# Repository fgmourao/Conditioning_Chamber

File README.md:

# A Custom Microcontrolled and Wireless-Operated Chamber for Auditory Fear Conditioning

Front. Neurosci., 07 November 2019<br />
Sec. Neural Technology <br />
https://doi.org/10.3389/fnins.2019.01193<br />

Correspondence:<br />

Flávio Afonso Gonçalves Mourão, PhD<br />
Núcleo de Neurociências, Departamento de Fisiologia e Biofísica<br />
Instituto de Ciências Biológicas (ICB)<br /> 
Universidade Federal de Minas Gerais (UFMG)<br />
Av. Antônio Carlos, 6627 - CEP 31270-901- Campus Pampulha<br />
Belo Horizonte - MG - Brazil<br />
Fax: +55 31 3409-2924 Phone: +55 31 3409-2927<br />
Email:  mourao.fg@gmail.com / fagm@ufmg.br <br />

Márcio Flávio Dutra Moraes, PhD<br />
Núcleo de Neurociências, Departamento de Fisiologia e Biofísica<br />
Instituto de Ciências Biológicas (ICB)<br /> 
Universidade Federal de Minas Gerais (UFMG)<br />
Av. Antônio Carlos, 6627 - CEP 31270-901- Campus Pampulha<br />
Belo Horizonte - MG - Brazil<br />
Fax: +55 31 3409-2924 Phone: +55 31 3409-2930<br />
Email: mfdm@icb.ufmg.br <br />
<br />

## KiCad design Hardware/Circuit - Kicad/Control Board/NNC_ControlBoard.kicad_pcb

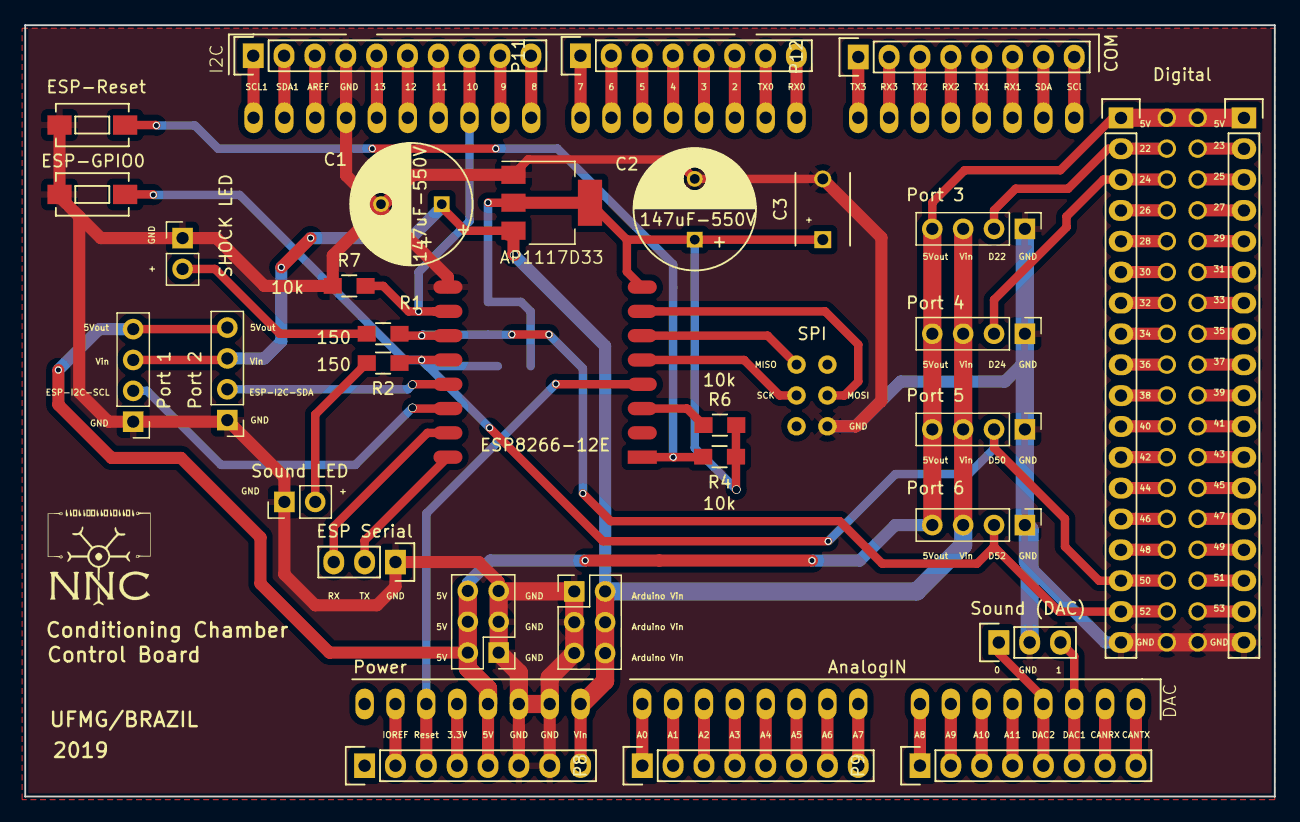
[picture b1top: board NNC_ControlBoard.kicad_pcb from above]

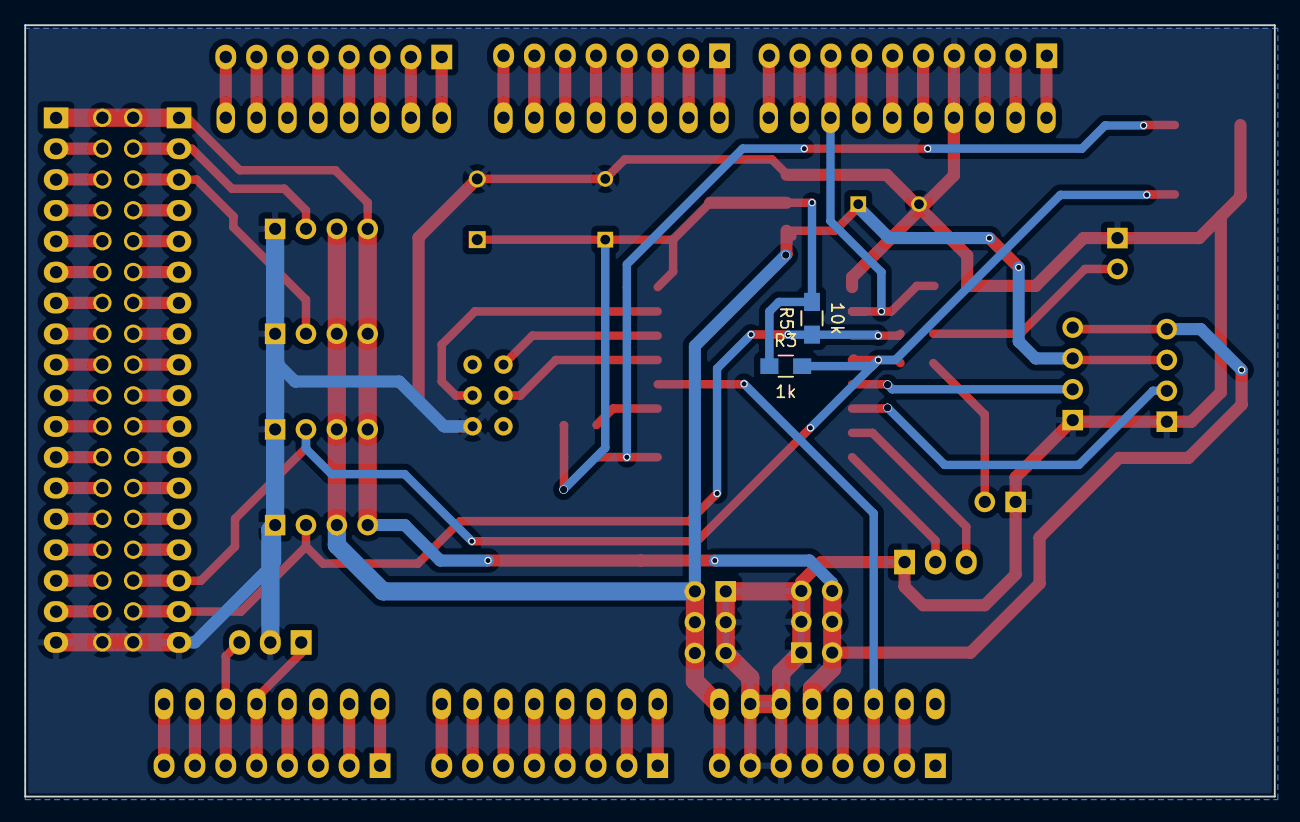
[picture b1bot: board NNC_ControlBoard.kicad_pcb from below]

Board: 2 copper layers, 102.9 x 63.5 mm, 35 parts (2 on the bottom side), 91 nets.

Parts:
C1, C2: 147uF-550V; C_Radial_D10_L13_P5
C3: C; C_Disc_D6_P5
Control Board: Conditioning Chamber; ARDUINO_DUE_SHIELD
D1: SHOCK LED; Pin_Header_Straight_1x02_Pitch2.54mm
D2: Sound LED; Pin_Header_Straight_1x02_Pitch2.54mm
ESP1: ESP8266-12E; ESP-12E_noBottomPads
ESP-GPIO0: 2; SW_SPST_EVQPE1
ESP-Reset: 1; SW_SPST_EVQPE1
I2C: PWM2; Pin_Header_Straight_1x10
J1: Port 6; Pin_Header_Straight_1x04_Pitch2.54mm
J2: Port 2; Pin_Header_Straight_1x04_Pitch2.54mm
J3: Port 3; Pin_Header_Straight_1x04_Pitch2.54mm
J4: Port 4; Pin_Header_Straight_1x04_Pitch2.54mm
J5: Port 5; Pin_Header_Straight_1x04_Pitch2.54mm
J6: Port 1; Pin_Header_Straight_1x04_Pitch2.54mm
J7: Arduino Vin; Pin_Header_Straight_2x03_Pitch2.54mm
J8: 5V; Pin_Header_Straight_2x03_Pitch2.54mm
P3: Sound (DAC); Pin_Header_Straight_1x03
P4: ESP Serial; Pin_Header_Straight_1x03
P5: DIG1; Pin_Header_Straight_1x18
P6: DIG2; Pin_Header_Straight_1x18
P7: Power; Pin_Header_Straight_1x08
P8: AnalogIN; Pin_Header_Straight_1x08
P9: DAC; Pin_Header_Straight_1x08
P11: PWM1; Pin_Header_Straight_1x08
P12: COM; Pin_Header_Straight_1x08
R1, R2: 150; R_0805_HandSoldering
R3: 1k; R_0805_HandSoldering
R4, R5, R6, R7: 10k; R_0805_HandSoldering
U1: AP1117D33; SOT-223-3_TabPin2

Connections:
/5Voutput: Control Board.5V, Control Board.5V_4, Control Board.5V_5, J1.4, J2.4, J3.4, J4.4, J5.4, J6.4, J8.2, J8.4, J8.6, P5.1, P6.1, P7.5
/Arduino_Vin: C1.1, Control Board.V_IN, J1.3, J2.3, J3.3, J4.3, J5.3, J6.3, J7.2, J7.4, J7.6, P7.8, U1.3
/D22: Control Board.22, J3.2, P5.2
/D23: Control Board.23, P6.2
/D24: Control Board.24, J4.2, P5.3
/D25: Control Board.25, P6.3
/D26: Control Board.26, P5.4
/D27: Control Board.27, P6.4
/D28: Control Board.28, P5.5
/D29: Control Board.29, P6.5
/D30: Control Board.30, P5.6
/D31: Control Board.31, P6.6
/D32: Control Board.32, P5.7
/D33: Control Board.33, P6.7
/D34: Control Board.34, P5.8
/D35: Control Board.35, P6.8
/D36: Control Board.36, P5.9
/D37: Control Board.37, P6.9
/D38: Control Board.38, P5.10
/D39: Control Board.39, P6.10
/D40: Control Board.40, P5.11
/D41: Control Board.41, P6.11
/D42: Control Board.42, P5.12
/D43: Control Board.43, P6.12
/D44: Control Board.44, P5.13
/D45: Control Board.45, P6.13
/D46: Control Board.46, P5.14
/D47: Control Board.47, P6.14
/D48: Control Board.48, P5.15
/D49: Control Board.49, P6.15
/D50: Control Board.50, ESP1.18, ESP-GPIO0.1, J5.2, P5.16, R2.1, R3.2
/D51: Control Board.51, P6.16
/D52: Control Board.52, ESP1.17, J1.2, P5.17, R1.1, R5.1
/D53: Control Board.53, P6.17
/DAC0: Control Board.DAC0, P3.1, P9.5
/DAC1: Control Board.DAC1, P3.3, P9.6
/ESP12Econfig/ESPchpd: ESP1.3, R6.1
/ESP12Econfig/ESPrst: ESP1.1, ESP-Reset.1, R4.2
/ESP12Econfig/VDD3V: C2.1, C3.1, ESP1.8, R3.1, R4.1, R5.2, R6.2, U1.2
/ESP_CS: Control Board.10, ESP1.16, I2C.8, R7.2
/ESP_GPIO16: Control Board.RST, ESP1.4, P7.3
/ESP_I2C_SCL: ESP1.20, J6.2
/ESP_I2C_SDA: ESP1.19, J2.2
/ESP_MISO: Control Board.SP1, ESP1.6
/ESP_MOSI: Control Board.SP4, ESP1.7
/ESP_RX: ESP1.21, P4.3
/ESP_SCK: Control Board.SP3, ESP1.5
/ESP_TX: ESP1.22, P4.2
/GND: C1.2, C2.2, C3.2, Control Board.GND1, Control Board.GND2, Control Board.GND3, Control Board.GND4, Control Board.GND5, Control Board.SP6, D1.1, D2.1, ESP1.15, ESP-GPIO0.2, ESP-Reset.2, I2C.4, J1.1, J2.1, J3.1, J4.1, J5.1, J6.1, J7.1, J7.3, J7.5, J8.1, J8.3, J8.5, P3.2, P4.1, P5.18, P6.18, P7.6, P7.7, R7.1, U1.1
unnamed: D1.2, R1.2
unnamed: D2.2, R2.2
unnamed: Control Board.IO_R, P7.2
unnamed: Control Board.3V3, P7.4
unnamed: Control Board.AD0, P8.1
unnamed: Control Board.AD1, P8.2
unnamed: Control Board.AD2, P8.3
unnamed: Control Board.AD3, P8.4
unnamed: Control Board.AD4, P8.5
unnamed: Control Board.AD5, P8.6
unnamed: Control Board.AD6, P8.7
unnamed: Control Board.AD7, P8.8
unnamed: Control Board.AD8, P9.1
unnamed: Control Board.AD9, P9.2
unnamed: Control Board.AD10, P9.3
unnamed: Control Board.AD11, P9.4
unnamed: Control Board.C_RX, P9.7
unnamed: Control Board.C_TX, P9.8
unnamed: Control Board.SCL1, I2C.1
unnamed: Control Board.SDA1, I2C.2
unnamed: Control Board.AREF, I2C.3
unnamed: Control Board.13, I2C.5
unnamed: Control Board.12, I2C.6
unnamed: Control Board.11, I2C.7
unnamed: Control Board.9, I2C.9
unnamed: Control Board.8, I2C.10
unnamed: Control Board.7, P11.1
unnamed: Control Board.6, P11.2
unnamed: Control Board.5, P11.3
unnamed: Control Board.4, P11.4
unnamed: Control Board.3, P11.5
unnamed: Control Board.2, P11.6
unnamed: Control Board.1, P11.7
unnamed: Control Board.0, P11.8
unnamed: Control Board.14, P12.1
unnamed: Control Board.15, P12.2
unnamed: Control Board.16, P12.3
unnamed: Control Board.17, P12.4
unnamed: Control Board.18, P12.5
unnamed: Control Board.19, P12.6
unnamed: Control Board.20, P12.7
unnamed: Control Board.21, P12.8

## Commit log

2023-06-27 Update_27-06-23
